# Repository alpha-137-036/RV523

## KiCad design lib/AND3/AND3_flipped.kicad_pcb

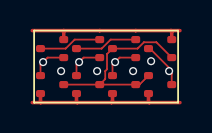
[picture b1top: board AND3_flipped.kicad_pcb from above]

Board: 2 copper layers, 8 parts (0 on the bottom side), 9 nets.

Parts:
nand1.N1, nand1.N2, nand1.N3: NMOS; SOT523
nand1.P1, nand1.P2, nand1.P3: PMOS; SOT523
not1.N1: NMOS; SOT523
not1.P1: PMOS; SOT523

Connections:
A1: nand1.N1.1 (G), nand1.P1.1 (G)
A2: nand1.N2.1 (G), nand1.P2.1 (G)
A3: nand1.N3.1 (G), nand1.P3.1 (G)
GND: nand1.N1.2 (S), not1.N1.2 (S)
VDD: nand1.P1.2 (S), nand1.P2.2 (S), nand1.P3.2 (S), not1.P1.2 (S)
Y: not1.N1.3 (D), not1.P1.3 (D)
nY: nand1.N3.3 (D), nand1.P1.3 (D), nand1.P2.3 (D), nand1.P3.3 (D), not1.N1.1 (G), not1.P1.1 (G)
nand1.int1: nand1.N1.3 (D), nand1.N2.2 (S)
nand1.int2: nand1.N2.3 (D), nand1.N3.2 (S)

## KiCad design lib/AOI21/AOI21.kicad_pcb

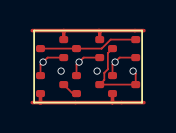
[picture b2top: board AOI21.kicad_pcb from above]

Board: 2 copper layers, 6 parts (0 on the bottom side), 8 nets.

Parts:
N1, N2, N3: NMOS; SOT523
P1, P2, P3: PMOS; SOT523

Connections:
A1: N1.1 (G), P1.1 (G)
A2: N2.1 (G), P2.1 (G)
B1: N3.1 (G), P3.1 (G)
GND: N1.2 (S), N3.2 (S)
VDD: P1.2 (S), P2.2 (S)
Y: N2.3 (D), N3.3 (D), P3.3 (D)
pndA: P1.3 (D), P2.3 (D), P3.2 (S)
sndA1: N1.3 (D), N2.2 (S)

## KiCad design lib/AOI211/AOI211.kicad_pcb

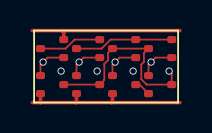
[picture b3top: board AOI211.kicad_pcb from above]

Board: 2 copper layers, 8 parts (0 on the bottom side), 9 nets.

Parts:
N1, N2, N3, N4: NMOS; SOT523
P1, P2, P3, P4: PMOS; SOT523

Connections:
A: N1.1 (G), P1.1 (G)
B: N2.1 (G), P2.1 (G)
C1: N3.1 (G), P3.1 (G)
C2: N4.1 (G), P4.1 (G)
GND: N1.2 (S), N2.2 (S), N3.2 (S)
Y: N1.3 (D), N2.3 (D), N4.3 (D), P3.3 (D), P4.3 (D)
intC: N3.3 (D), N4.2 (S)
intPA: P1.3 (D), P2.2 (S)
intPB: P2.3 (D), P3.2 (S), P4.2 (S)
